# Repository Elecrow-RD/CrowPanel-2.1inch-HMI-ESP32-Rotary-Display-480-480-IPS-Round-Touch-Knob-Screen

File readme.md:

### 1, Product picture

### 2, Product version number

|      | Hardware | Software | Remark |
| ---- | -------- | -------- | ------ |
| 1    | V1.0     | V1.0     | latest |

### 3, product information

#### Display Module Specifications

| Main Chip: ESP32-S3R8      |                                                              |
| -------------------------- | ------------------------------------------------------------ |
| Processor                  | Equipped with high-performance Xtensa 32-bit LX7 dual-core processor, with a main frequency of up to 240MHz |
| System memory              | 512KB SRAM、8M PSRAM                                         |
| Storage                    | 16M Flash                                                    |
| **Screen**                 |                                                              |
| Size                       | 2.1 inch                                                     |
| Screen Type                | IPS                                                          |
| Touch Type                 | Capacitive Touch                                             |
| Resolution                 | 480*480                                                      |
| **Wireless Communication** |                                                              |
| Bluetooth                  | Bluetooth Low Energy and Bluetooth 5.0                       |
| WiFi                       | Support 802.11a/b/g/n，2.4GH                                 |
| **Hardware**               |                                                              |
| UART Interface             | 1x UART1, 1x UART0; ZX-MX 1.25-4P                            |
| I2C Interface              | ZX-MX 1.25-4P                                                |
| FPC connector              | 12P, Power supply burning port                               |
| Button                     | RESET button, BOOT button, confirmation button (knob press switch) |
| LED Light                  | Power indicator, LED ambient light                           |
| **Other**                  |                                                              |
| Power Input                | 5V/1A                                                        |
| Operating temperature      | -20~65℃                                                      |
| Storage temperature        | -40~80℃                                                      |
| Operation Power            | Module: DC5VMain Chip: 3.3V                                  |
| Size                       | 79\*79*30mm                                                   |
| Shell                      | Aluminum alloy + plastic + acrylic                           |
| Net Weight                 | 80g                                                          |

### 4, Use the driver module

| Name | dependency library |
| ---- | ------------------ |
| LVGL | lvgl/lvgl@8.3.11   |

### 5,Quick Start

##### Arduino IDE starts

1.Download the library files used by this product to the 'libraries' folder.

C:\Users\Documents\Arduino\libraries\

2.Open the Arduino IDE

3.Open the code configuration environment and burn it.

### 6,Folder structure.

|--3D file： Contains 3D model files (.stp) for the hardware. These files can be used for visualization, enclosure design, or integration into CAD software.

|--Datasheet: Includes datasheets for components used in the project, providing detailed specifications, electrical characteristics, and pin configurations.

|--Eagle_SCH&PCB: Contains **Eagle CAD** schematic (`.sch`) and PCB layout (`.brd`) files. These are used for circuit design and PCB manufacturing.

|--example: Provides example code and projects to demonstrate how to use the hardware and libraries. These examples help users get started quickly.

|--factory_firmware: Stores pre-compiled factory firmware that can be directly flashed onto the device. This ensures the device runs the default functionality.

|--factory_sourcecode: Contains the source code for the factory firmware, allowing users to modify and rebuild the firmware as needed.

### 7,Pin definition

- I2C_SDA_PIN: 38

- I2C_SCL_PIN: 39

- ENCODER_A_PIN: 42

- ENCODER_B_PIN: 4

- SCREEN_BACKLIGHT_PIN: 6

PCF8574 Extended IO (via I2C address 0x21):

 \- P0:Touchscreen reset

\- P2: Touchscreen interrupt

\- P3: LCD power

\- P4: LCD reset

\- P5: Encoder button (INPUT_PULLUP)

LCD Bus-related（Arduino_ESP32RGBPanel）：

- 1, 2, 3, 5, 7, 8, 9, 10, 11, 12, 13, 14, 15, 16, 17, 18, 21, 40, 41, 45, 46, 47, 48

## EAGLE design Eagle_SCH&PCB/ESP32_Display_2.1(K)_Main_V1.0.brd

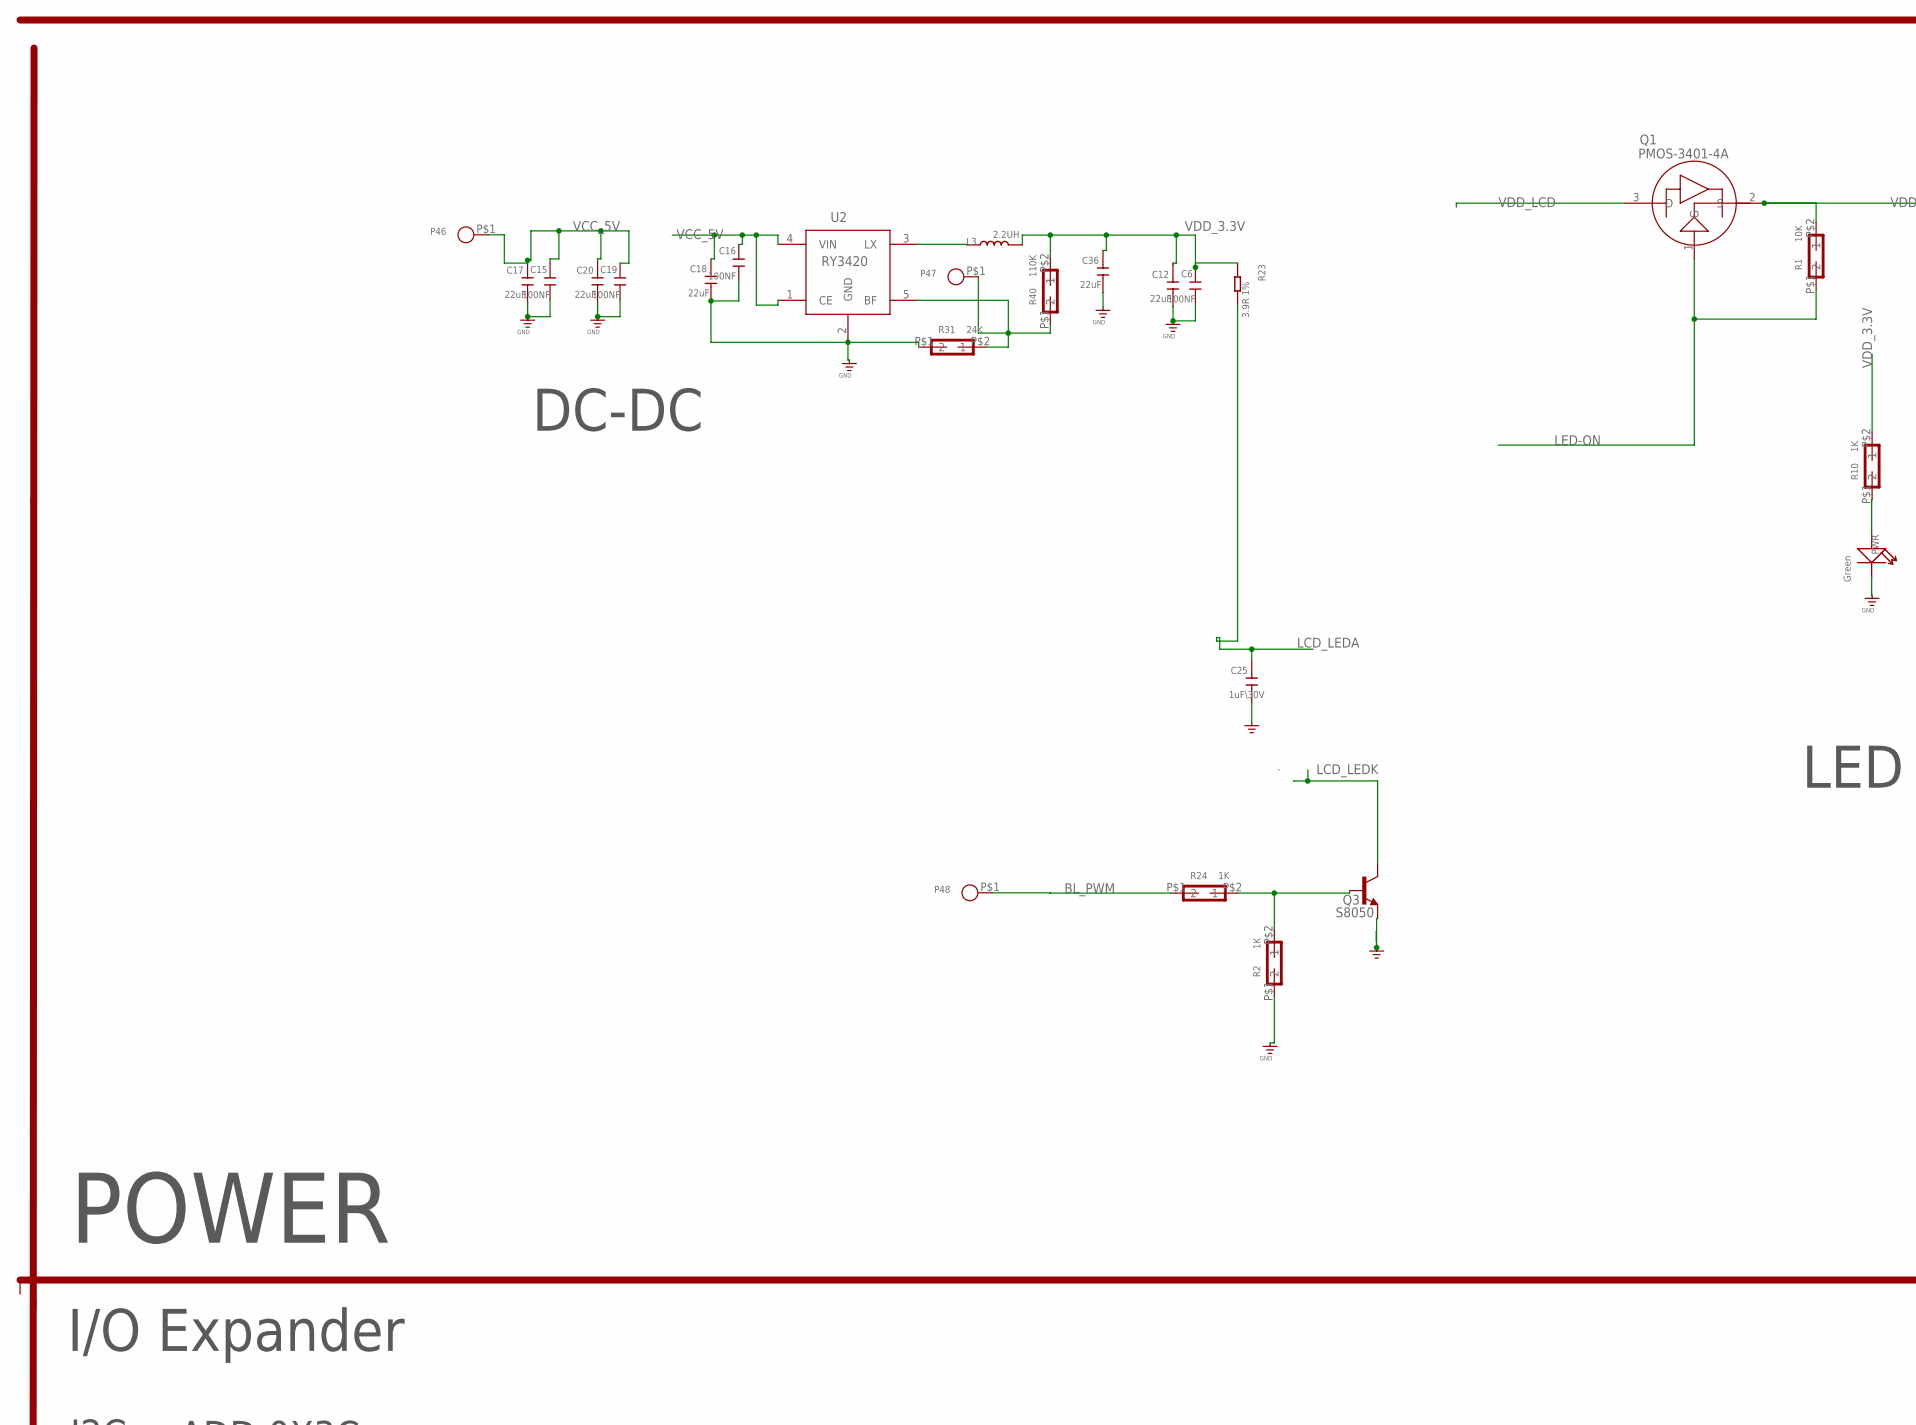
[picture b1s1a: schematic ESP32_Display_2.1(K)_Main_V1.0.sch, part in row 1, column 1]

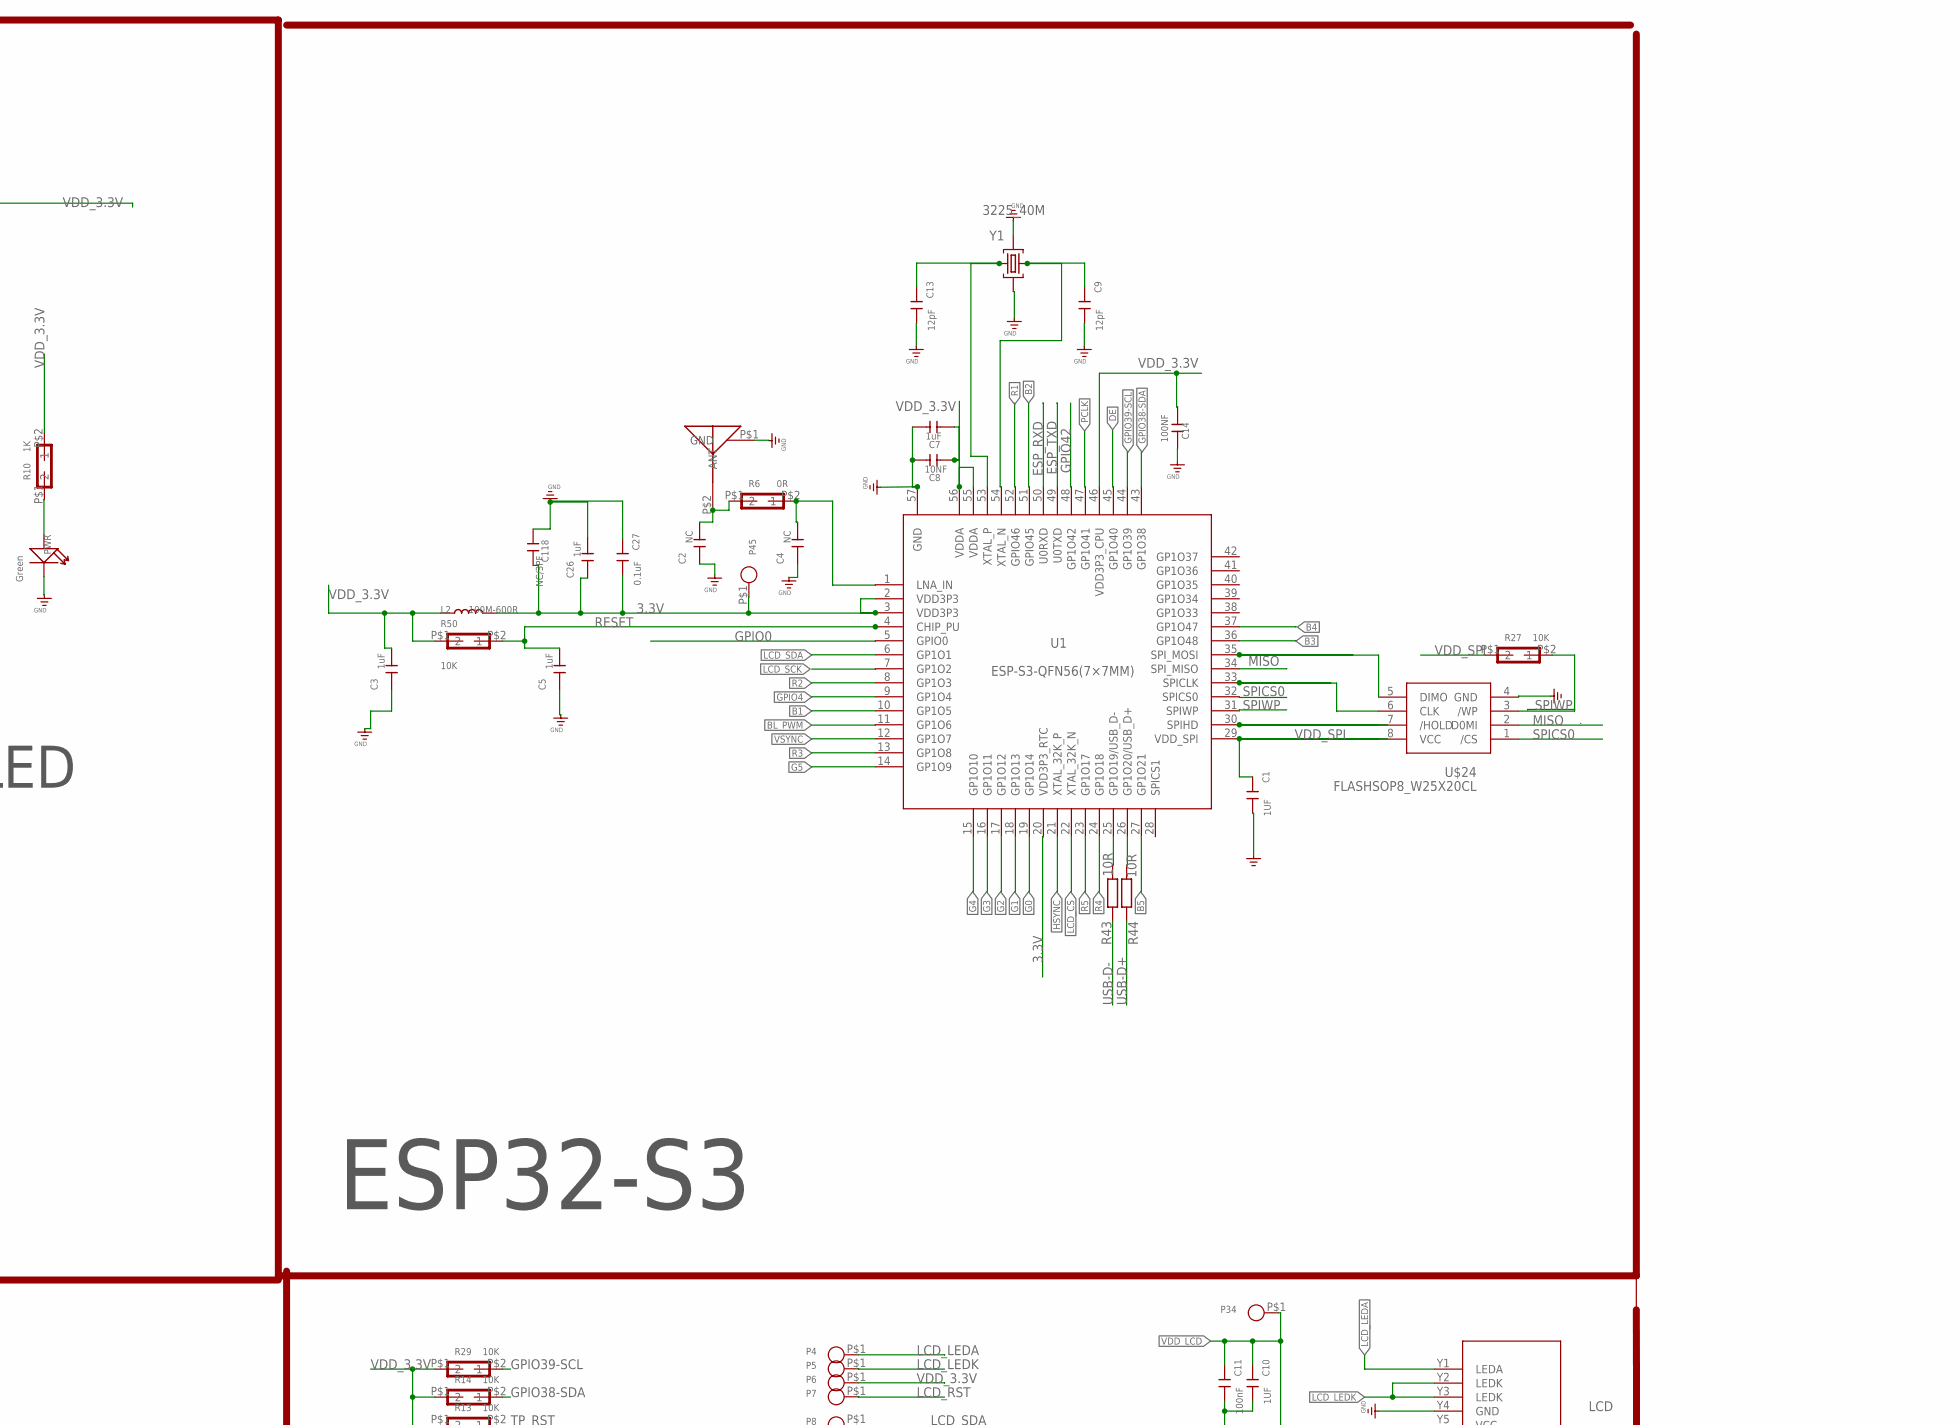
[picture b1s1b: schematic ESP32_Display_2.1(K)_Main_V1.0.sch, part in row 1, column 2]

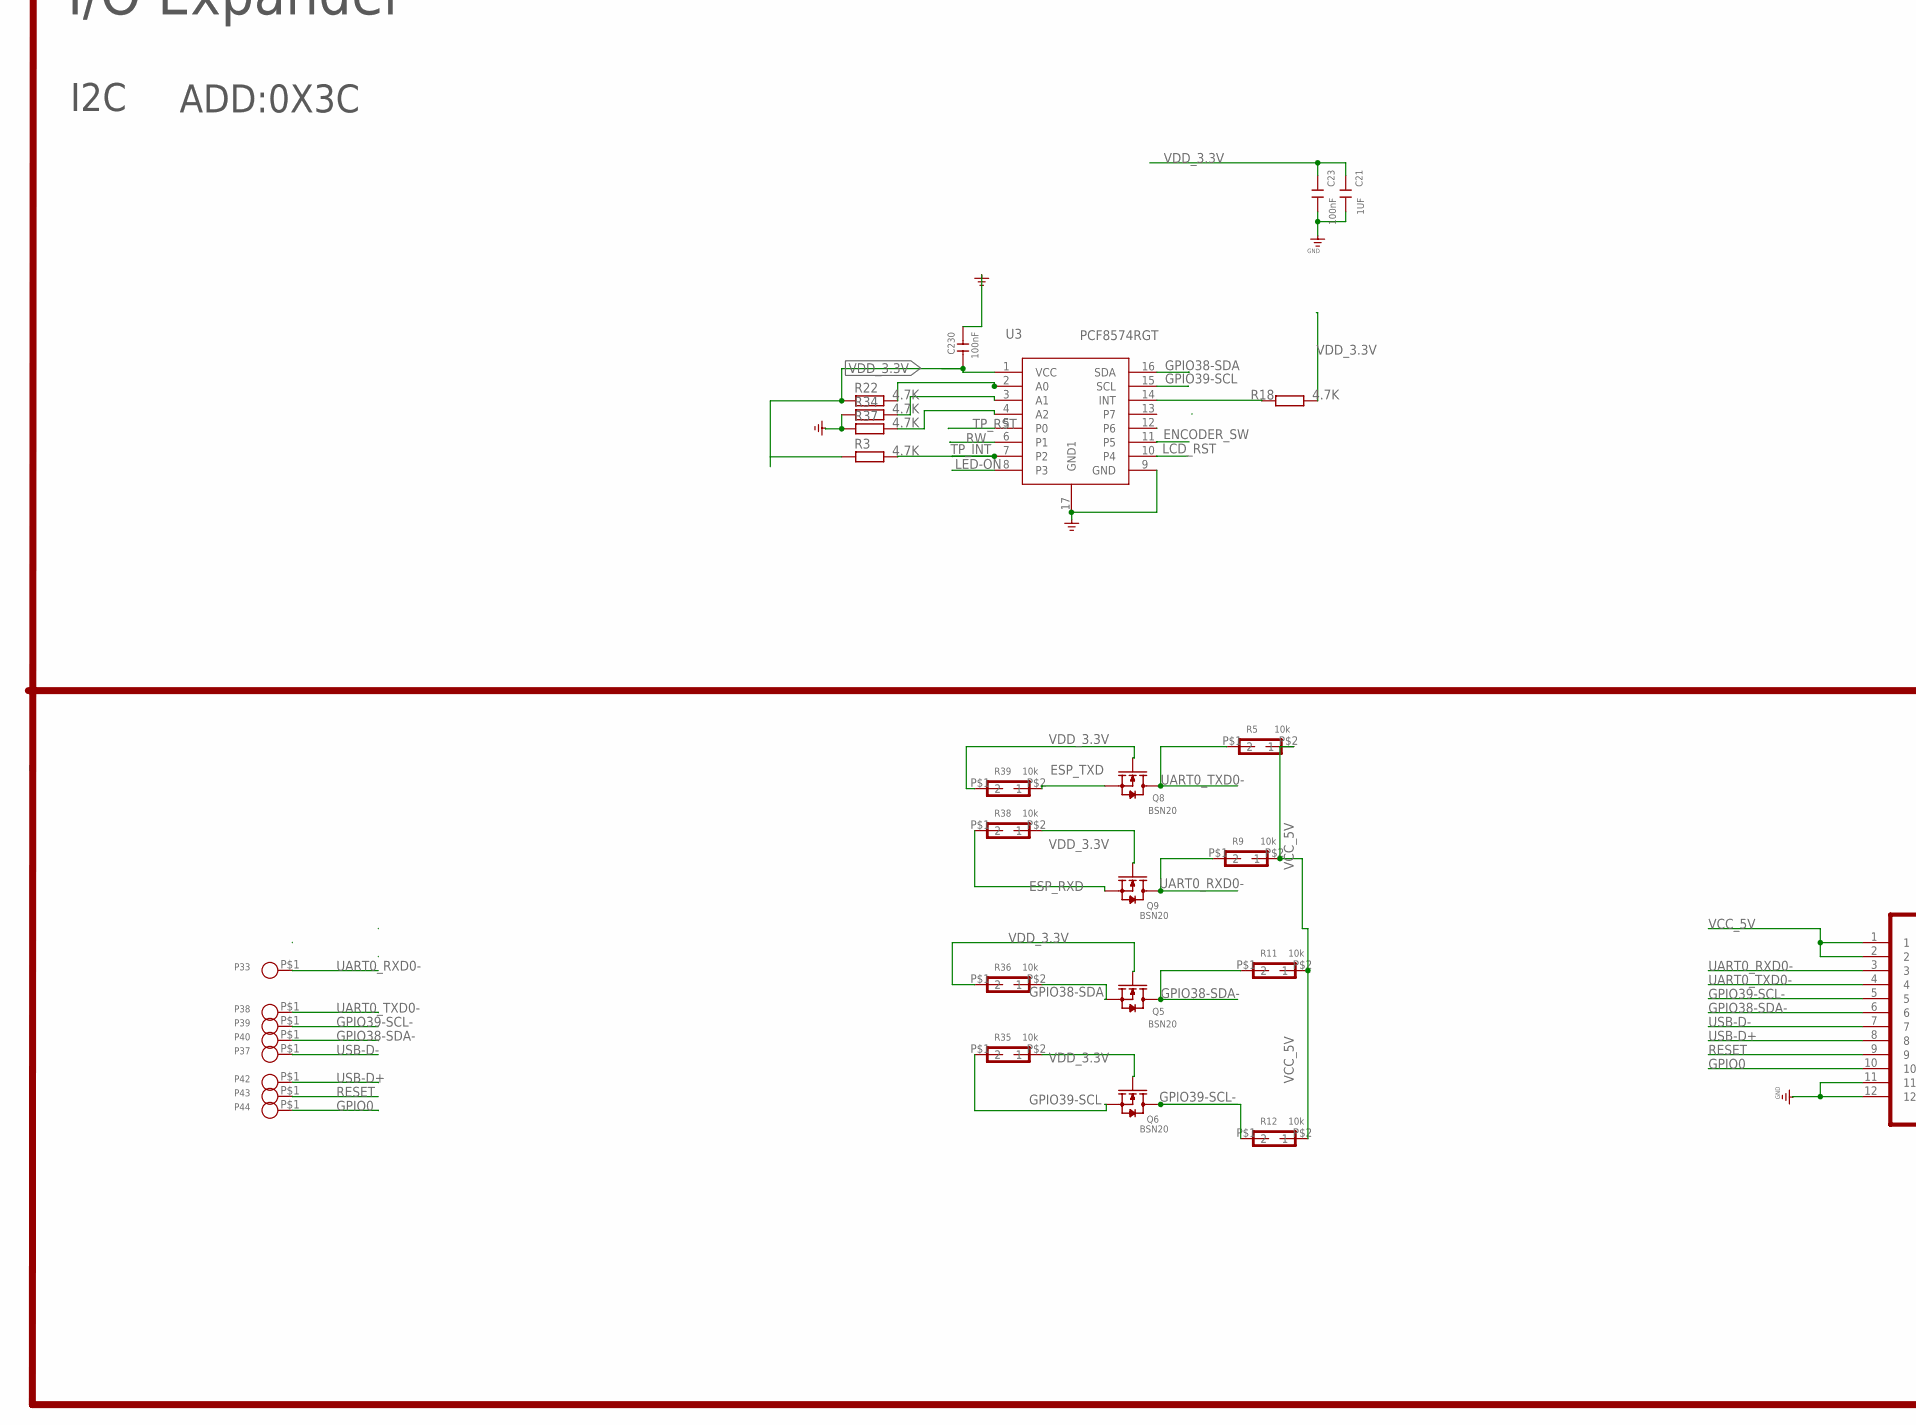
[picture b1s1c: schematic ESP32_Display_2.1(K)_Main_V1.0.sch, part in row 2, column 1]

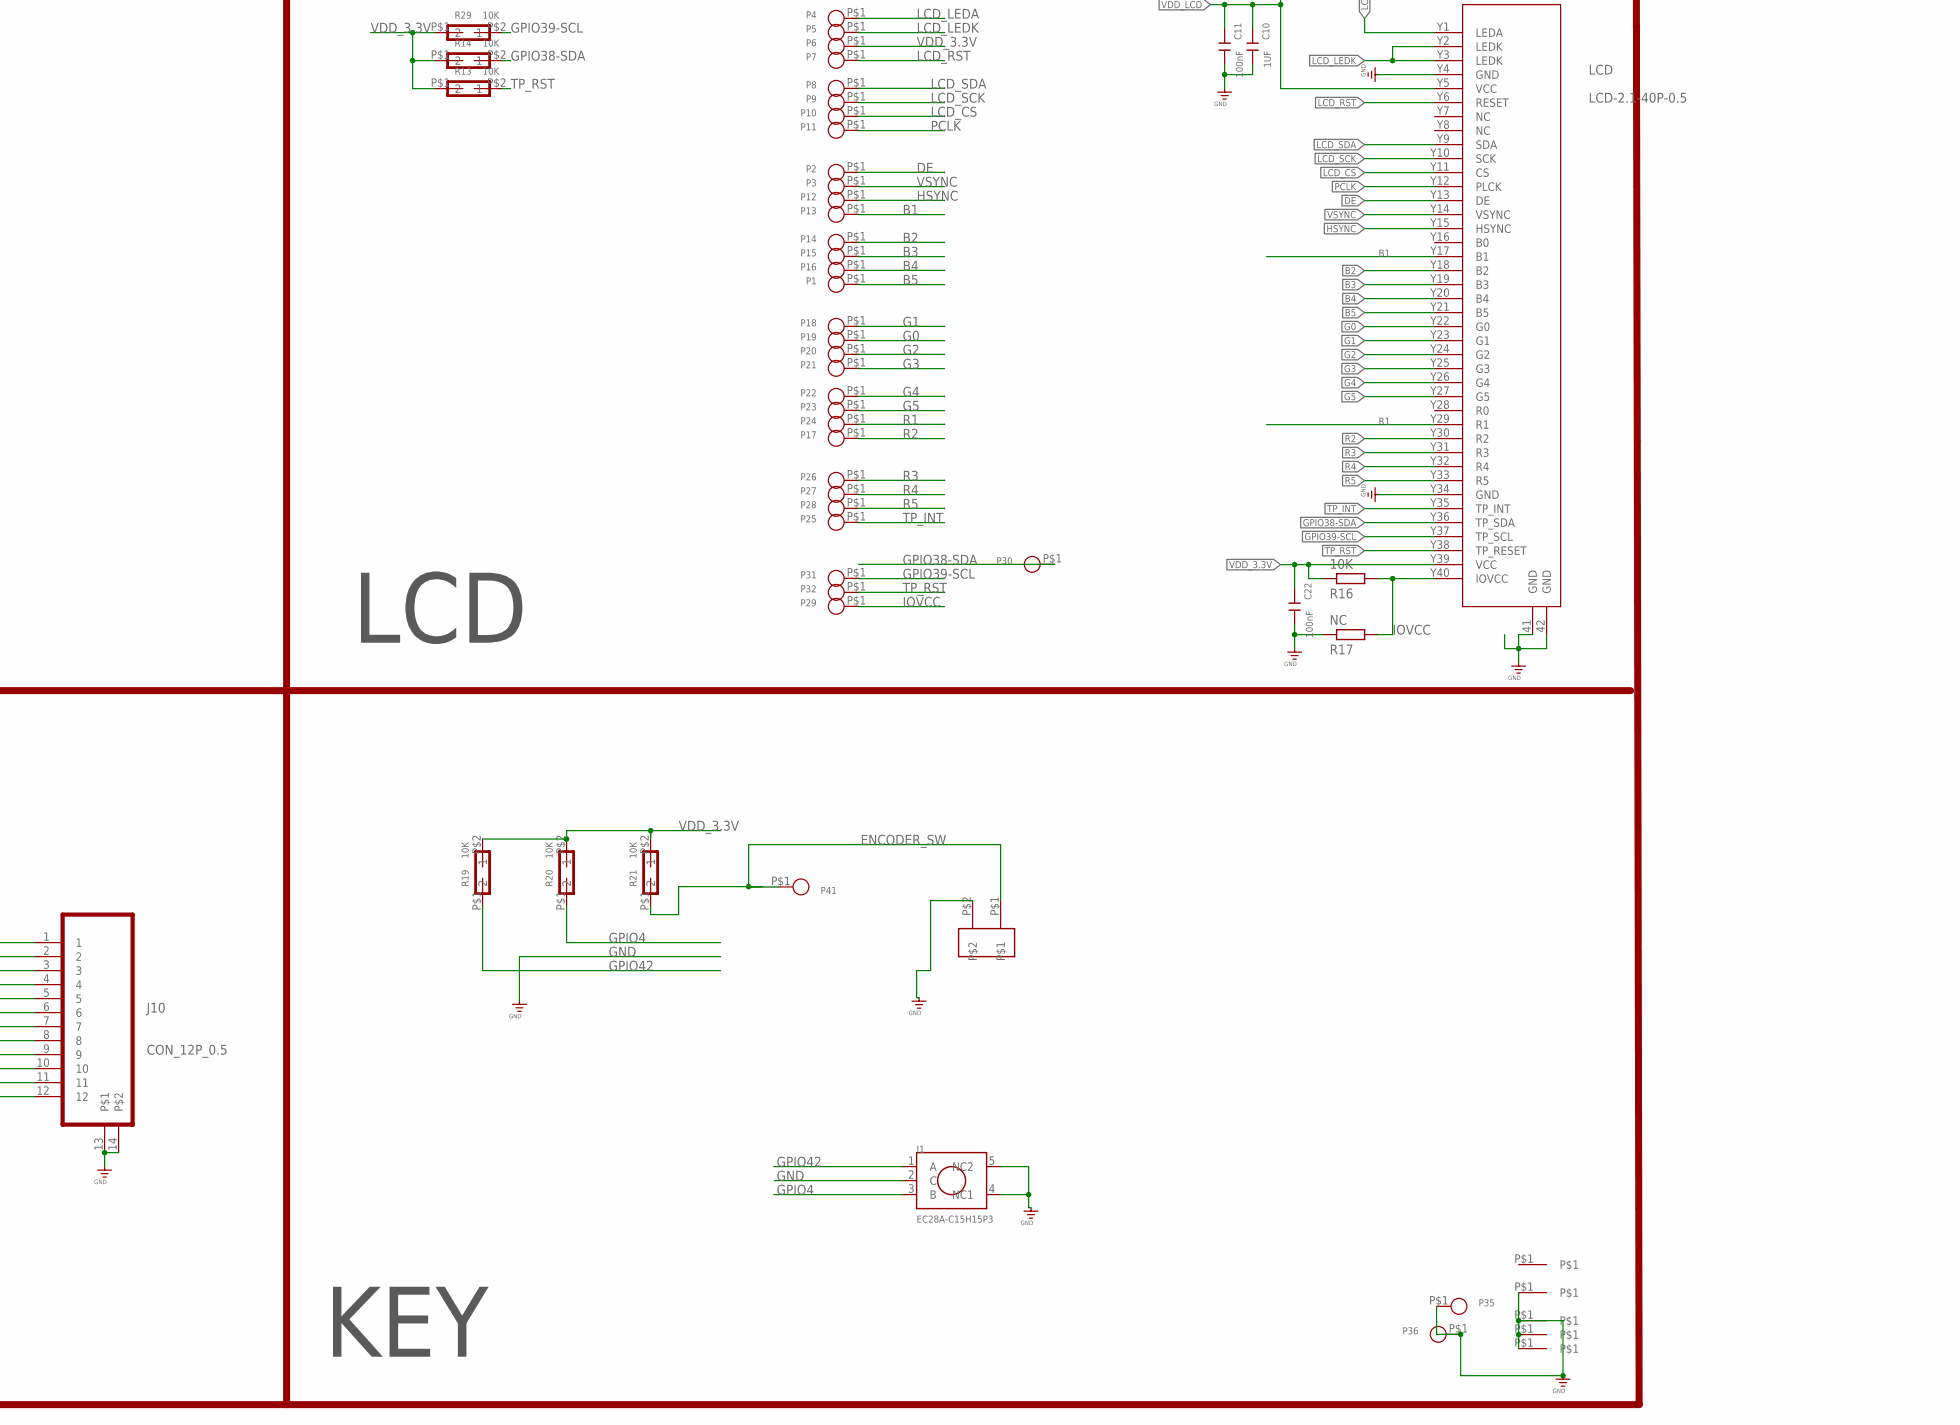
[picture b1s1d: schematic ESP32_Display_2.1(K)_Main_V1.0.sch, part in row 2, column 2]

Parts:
ANT: BT_ANT
C1, C10, C21: 1UF; 0402
C2, C4: NC; C0402
C3, C5, C26: 1uF; C0402
C6, C15, C16, C19: 100NF; 0603
C7: 1uF; C0603
C8: 10NF; C0603
C9, C13: 12pF; 0402
C11, C22, C23: 100nF; 0402
C12, C17, C18, C20, C36: 22uF; 0805
C14: 100NF; C0603
C25: 1uF\30V; 0805
C27: 0.1uF; 0402
C118: NC/3PF; 0603
C230: 100nF; C0603
J1: EC28A-C15H15P3
J10: CON_12P_0.5; 0.5MM-12P
K112: BUTTON_2P
L2: 100M-600R; L0603
L3: 2.2UH; L0420
LCD: LCD-2.1-40P-0.5; 0.5MM-40P
P1, P2, P3, P4, P5, P6, P7, P8, P9, P10, P11, P12, P13, P14, P15, P16, P17, P18, P19, P20, P21, P22, P23, P24, P25, P26, P27, P28, P29, P30, P31, P32, P33, P34, P35, P36, P37, P38, P39, P40, P41, P42, P43, P44, P45, P46, P47, P48: PADPAD-1.0MM; PAD-1.0MM
PWR: Green; LED-0603
Q1: PMOS-3401-4A; SOT-23
Q3: S8050; SPARKFUN_SOT23
Q5, Q6, Q8, Q9: BSN20; SOT23
R1, R13, R14, R19, R20, R21, R27, R29, R50: 10K; 0402
R2, R10, R24: 1K; 0402
R3, R18, R22, R34, R37: 4.7K; R0402
R5, R9, R11, R12, R35, R36, R38, R39: 10k; 0402
R6: 0R; 0402
R16: 10K; R0402
R17: NC; R0402
R23: 3.9R 1%; DISCRETE_R0603
R31: 24K; 0402
R40: 110K; 0402
R43, R44: 10R; R0402
U1: ESP-S3-QFN56(7×7MM)
U2: RY3420; SOT23-5
U3: PCF8574RGT; QFN16-3*3
U$9, U$19, U$29, U$30, U$32: T-2-1.1
U$24: FLASHSOP8_W25X20CL; FLASHSOP8_SOP8
Y1: 3225_40M; CRYSTAL-3.2-2.5

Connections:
3.3V: C26.1, C27.2, C118.2, L2.2, P45.P$1, U1.2 (VDD3P3), U1.3 (VDD3P3), U1.20 (VDD3P3_RTC)
B1: LCD.Y17 (B1), P13.P$1, U1.10 (GP1O5)
B2: LCD.Y18 (B2), P14.P$1, U1.51 (GPIO45)
B3: LCD.Y19 (B3), P15.P$1, U1.36 (GP1O48)
B4: LCD.Y20 (B4), P16.P$1, U1.37 (GP1O47)
B5: LCD.Y21 (B5), P1.P$1, U1.27 (GP1O21)
BL_PWM: P48.P$1, R24.P$1 (1), U1.11 (GP1O6)
DE: LCD.Y13 (DE), P2.P$1, U1.45 (GP1O40)
ENCODER_A: U3.12 (P6)
ENCODER_SW: K112.P$1, P41.P$1, R21.P$1 (1), U3.11 (P5)
ESP_RXD: Q9.2 (S), R38.P$1 (1), U1.50 (U0RXD)
ESP_TXD: Q8.2 (S), R39.P$2 (2), U1.49 (U0TXD)
G0: LCD.Y22 (G0), P19.P$1, U1.19 (GP1O14)
G1: LCD.Y23 (G1), P18.P$1, U1.18 (GP1O13)
G2: LCD.Y24 (G2), P20.P$1, U1.17 (GP1O12)
G3: LCD.Y25 (G3), P21.P$1, U1.16 (GP1O11)
G4: LCD.Y26 (G4), P22.P$1, U1.15 (GP1O10)
G5: LCD.Y27 (G5), P23.P$1, U1.14 (GP1O9)
GND: ANT.P$1 (GND), C1.2, C2.1, C3.1, C4.1, C5.1, C6.2, C7.2, C8.2, C9.2, C10.2, C11.2, C12.1, C13.2, C14.2, C15.2, C16.2, C17.1, C18.1, C19.2, C20.1, C21.2, C22.2, C23.2, C25.1, C26.2, C27.1, C36.1, C118.1, C230.1, J1.2 (C), J1.4 (NC1), J1.5 (NC2), J10.11, J10.12, J10.13, J10.14, K112.P$2, LCD.41 (GND), LCD.42 (GND), LCD.Y4 (GND), LCD.Y34 (GND), P35.P$1, P36.P$1, PWR.-, Q3.2 (E), R2.P$1 (1), R17.2, R31.P$1 (1), R34.2, R37.2, U1.57 (GND), U2.2 (GND), U3.9 (GND), U3.17 (GND1), U$9.P$1, U$19.P$1, U$24.4 (GND), U$29.P$1, U$32.P$1, Y1.2 (GND), Y1.4 (GND)
GPIO0: J10.10, P44.P$1, U1.5 (GPIO0)
GPIO4: J1.3 (B), R20.P$1 (1), U1.9 (GP1O4)
GPIO38-SDA: LCD.Y36 (TP_SDA), P30.P$1, Q5.2 (S), R14.P$2 (2), R36.P$2 (2), U1.43 (GP1O38), U3.16 (SDA)
GPIO38-SDA-: J10.6, P40.P$1, Q5.3 (D), R11.P$1 (1)
GPIO39-SCL: LCD.Y37 (TP_SCL), P31.P$1, Q6.2 (S), R29.P$2 (2), R35.P$1 (1), U1.44 (GP1O39), U3.15 (SCL)
GPIO39-SCL-: J10.5, P39.P$1, Q6.3 (D), R12.P$1 (1)
GPIO42: J1.1 (A), R19.P$1 (1), U1.48 (GP1O42)
HSYNC: LCD.Y15 (HSYNC), P12.P$1, U1.21 (XTAL_32K_P)
IOVCC: LCD.Y40 (IOVCC), P29.P$1, R16.1, R17.1
LCD_CS: LCD.Y11 (CS), P10.P$1, U1.22 (XTAL_32K_N)
LCD_LEDA: C25.2, LCD.Y1 (LEDA), P4.P$1, R23.2
LCD_LEDK: LCD.Y2 (LEDK), LCD.Y3 (LEDK), P5.P$1, Q3.3 (C)
LCD_RST: LCD.Y6 (RESET), P7.P$1, U3.10 (P4)
LCD_SCK: LCD.Y10 (SCK), P9.P$1, U1.7 (GP1O2)
LCD_SDA: LCD.Y9 (SDA), P8.P$1, U1.6 (GP1O1)
LED-ON: Q1.1 (G), R1.P$1 (1), U3.8 (P3)
MISO: U1.34 (SPI_MISO), U$24.2 (D0MI)
unnamed: L3.1, U2.3 (LX)
unnamed: R22.1, U3.2 (A0)
unnamed: PWR.+, R10.P$1 (1)
unnamed: ANT.P$2 (ANT), C2.2, R6.P$1 (1)
unnamed: R43.2, U1.25 (GP1O19/USB_D-)
unnamed: P47.P$1, R31.P$2 (2), R40.P$1 (1), U2.5 (BF)
unnamed: R44.2, U1.26 (GP1O20/USB_D+)
unnamed: R34.1, U3.3 (A1)
unnamed: R37.1, U3.4 (A2)
unnamed: R18.2, U3.14 (INT)
unnamed: Q3.1 (B), R2.P$2 (2), R24.P$2 (2)
unnamed: U1.30 (SPIHD), U$24.7 (/HOLD)
unnamed: C4.2, R6.P$2 (2), U1.1 (LNA_IN)
unnamed: U1.33 (SPICLK), U$24.6 (CLK)
unnamed: U1.35 (SPI_MOSI), U$24.5 (DIMO)
unnamed: C13.1, U1.53 (XTAL_P), Y1.3 (C2)
unnamed: C9.1, U1.54 (XTAL_N), Y1.1 (C1)
PCLK: LCD.Y12 (PLCK), P11.P$1, U1.47 (GP1O41)
R1: LCD.Y29 (R1), P24.P$1, U1.52 (GPIO46)
R2: LCD.Y30 (R2), P17.P$1, U1.8 (GP1O3)
R3: LCD.Y31 (R3), P26.P$1, U1.13 (GP1O8)
R4: LCD.Y32 (R4), P27.P$1, U1.24 (GP1O18)
R5: LCD.Y33 (R5), P28.P$1, U1.23 (GP1O17)
RESET: C5.2, J10.9, P43.P$1, R50.P$2 (2), U1.4 (CHIP_PU)
RW: U3.6 (P1)
SPICS0: U1.32 (SPICS0), U$24.1 (/CS)
SPIWP: R27.P$2 (2), U1.31 (SPIWP), U$24.3 (/WP)
TP_INT: LCD.Y35 (TP_INT), P25.P$1, R3.1, U3.7 (P2)
TP_RST: LCD.Y38 (TP_RESET), P32.P$1, R13.P$2 (2), U3.5 (P0)
UART0_RXD0-: J10.3, P33.P$1, Q9.3 (D), R9.P$1 (1)
UART0_TXD0-: J10.4, P38.P$1, Q8.3 (D), R5.P$1 (1)
USB-D+: J10.8, P42.P$1, R44.1
USB-D-: J10.7, P37.P$1, R43.1
VCC_5V: C15.1, C16.1, C17.2, C18.2, C19.1, C20.2, J10.1, J10.2, P46.P$1, R5.P$2 (2), R9.P$2 (2), R11.P$2 (2), R12.P$2 (2), U2.1 (CE), U2.4 (VIN)
VDD_3.3V: C3.2, C6.1, C7.1, C8.1, C12.2, C14.1, C21.1, C22.1, C23.1, C36.2, C230.2, L2.1, L3.2, LCD.Y39 (VCC), P6.P$1, Q1.2 (S), Q5.1 (G), Q6.1 (G), Q8.1 (G), Q9.1 (G), R1.P$2 (2), R3.2, R10.P$2 (2), R13.P$1 (1), R14.P$1 (1), R16.2, R18.1, R19.P$2 (2), R20.P$2 (2), R21.P$2 (2), R22.2, R23.1, R29.P$1 (1), R35.P$2 (2), R36.P$1 (1), R38.P$2 (2), R39.P$1 (1), R40.P$2 (2), R50.P$1 (1), U1.46 (VDD3P3_CPU), U1.55 (VDDA), U1.56 (VDDA), U3.1 (VCC)
VDD_LCD: C10.1, C11.1, LCD.Y5 (VCC), P34.P$1, Q1.3 (D)
VDD_SPI: C1.1, R27.P$1 (1), U1.29 (VDD_SPI), U$24.8 (VCC)
VSYNC: LCD.Y14 (VSYNC), P3.P$1, U1.12 (GP1O7)

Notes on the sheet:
LED
ESP32-S3
LCD
DC-DC
POWER
KEY
I/O Expander
I2C
ADD:0X3C

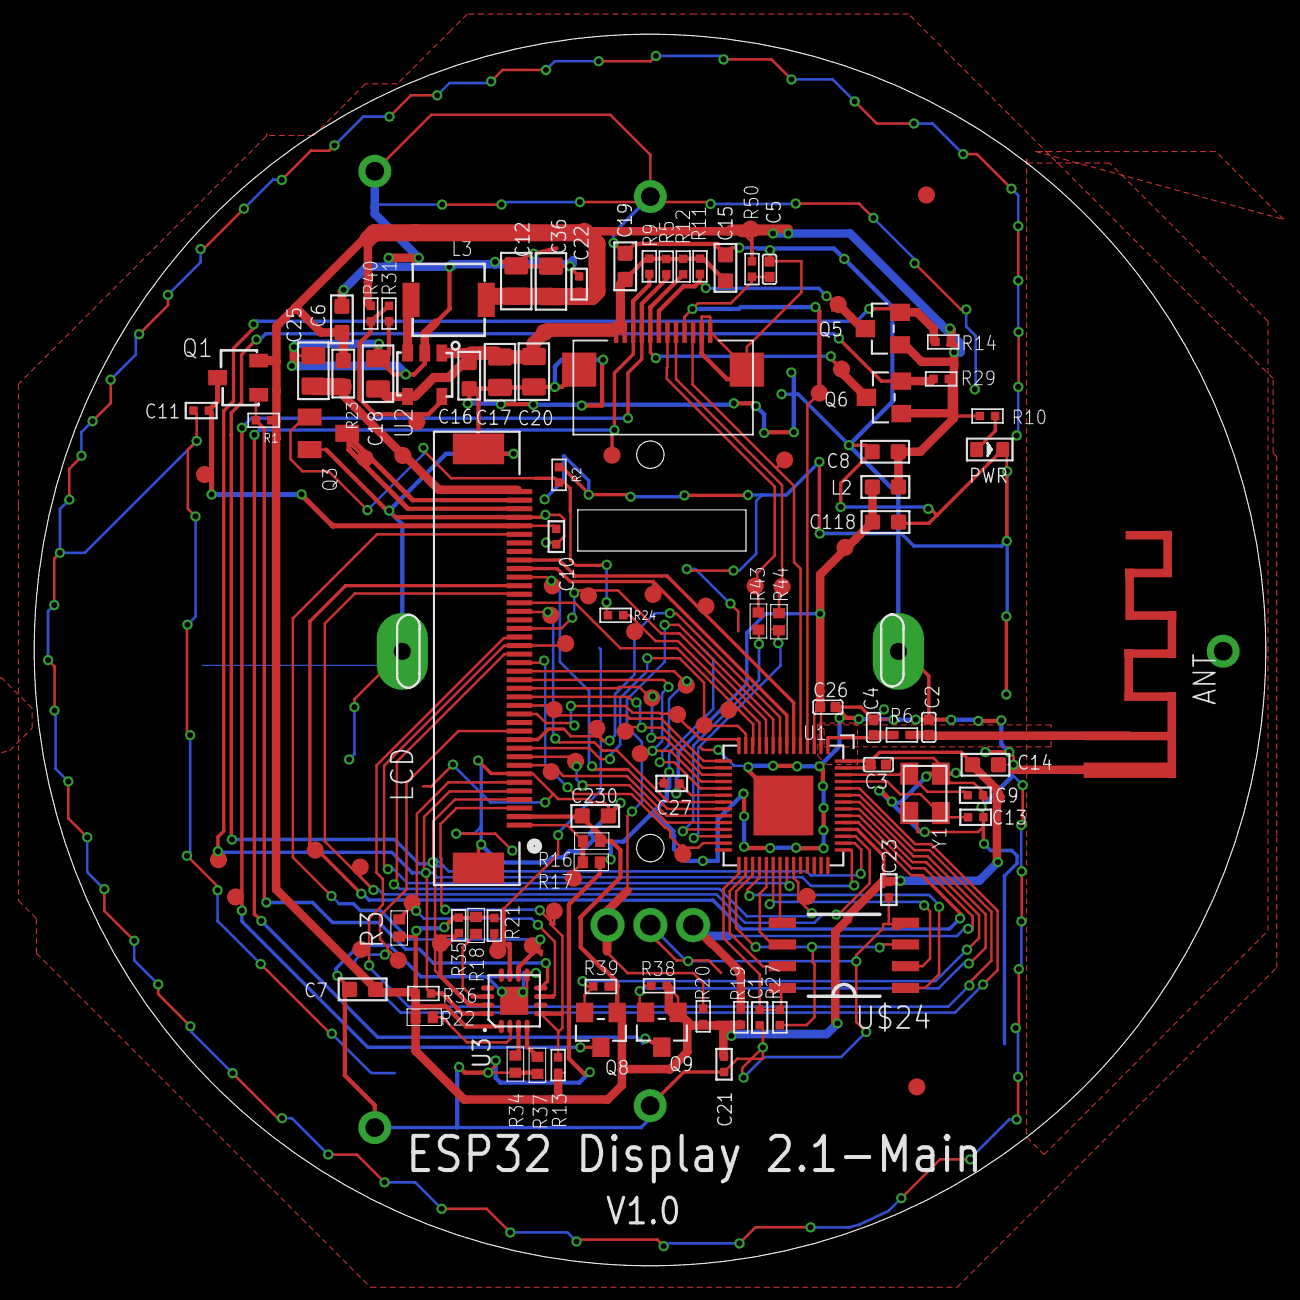
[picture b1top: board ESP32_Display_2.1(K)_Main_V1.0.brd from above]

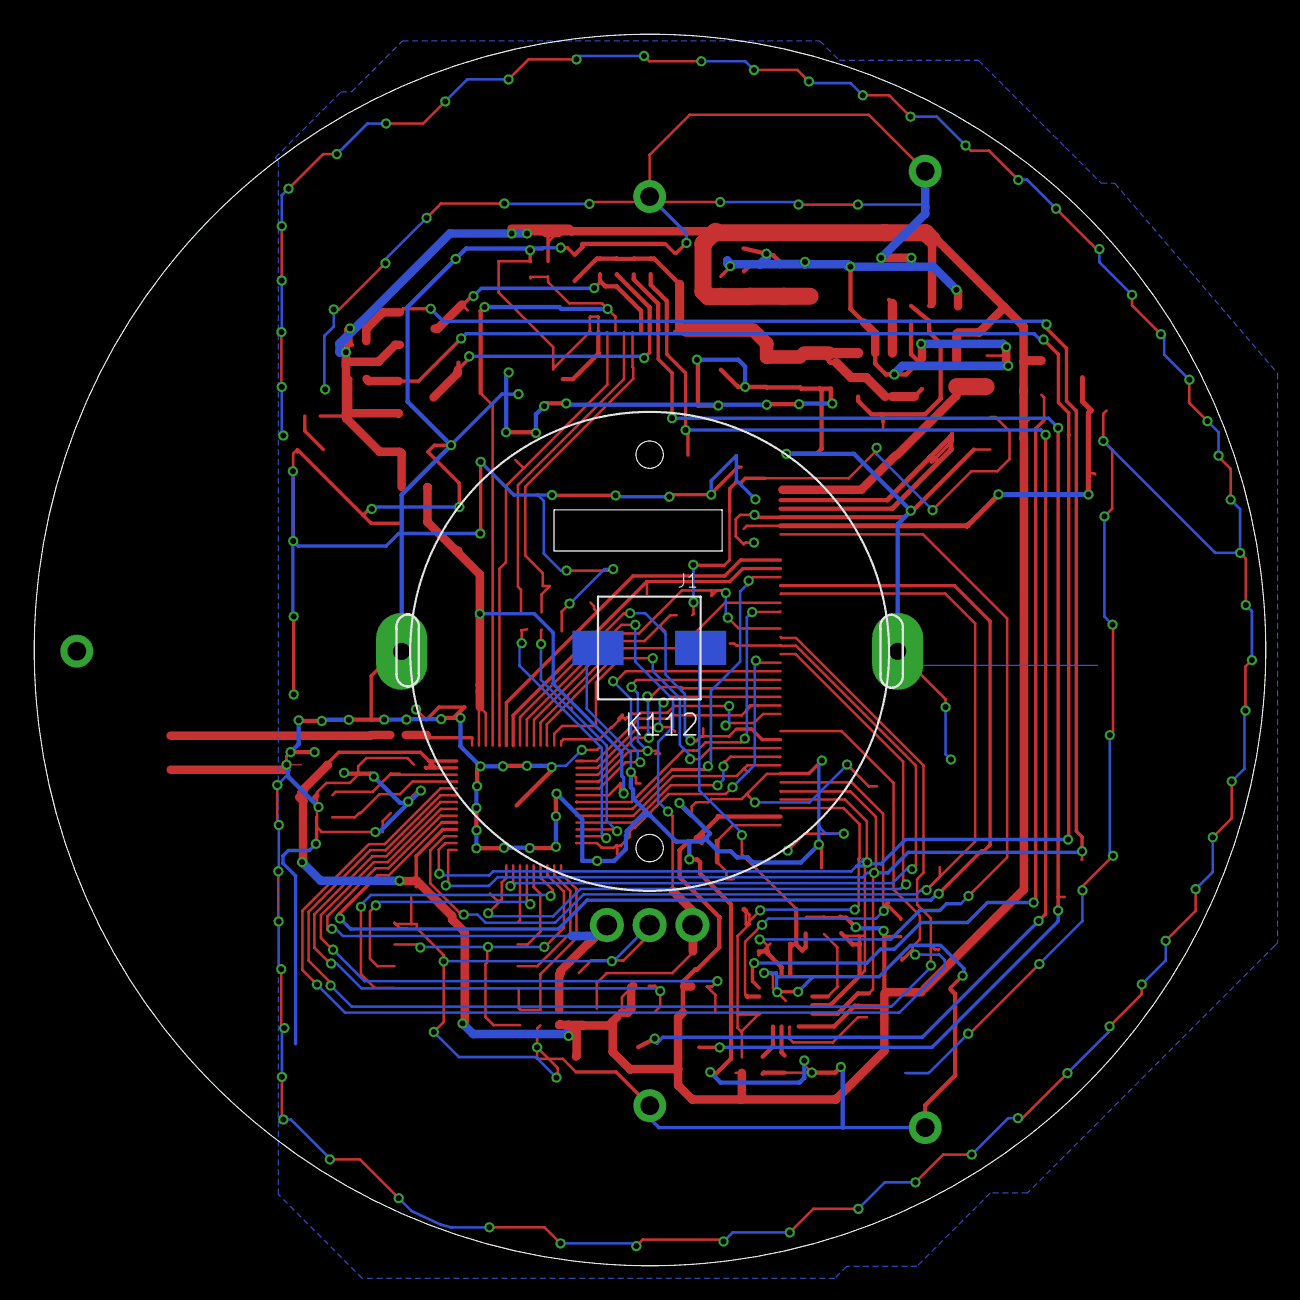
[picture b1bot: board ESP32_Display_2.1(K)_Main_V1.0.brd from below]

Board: 2 copper layers, 72.0 x 72.0 mm, 134 parts (3 on the bottom side), 72 nets.
